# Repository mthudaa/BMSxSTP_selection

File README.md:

# BMSxSTP_selection
This repository used for BMS project at STP ITS selection purpose

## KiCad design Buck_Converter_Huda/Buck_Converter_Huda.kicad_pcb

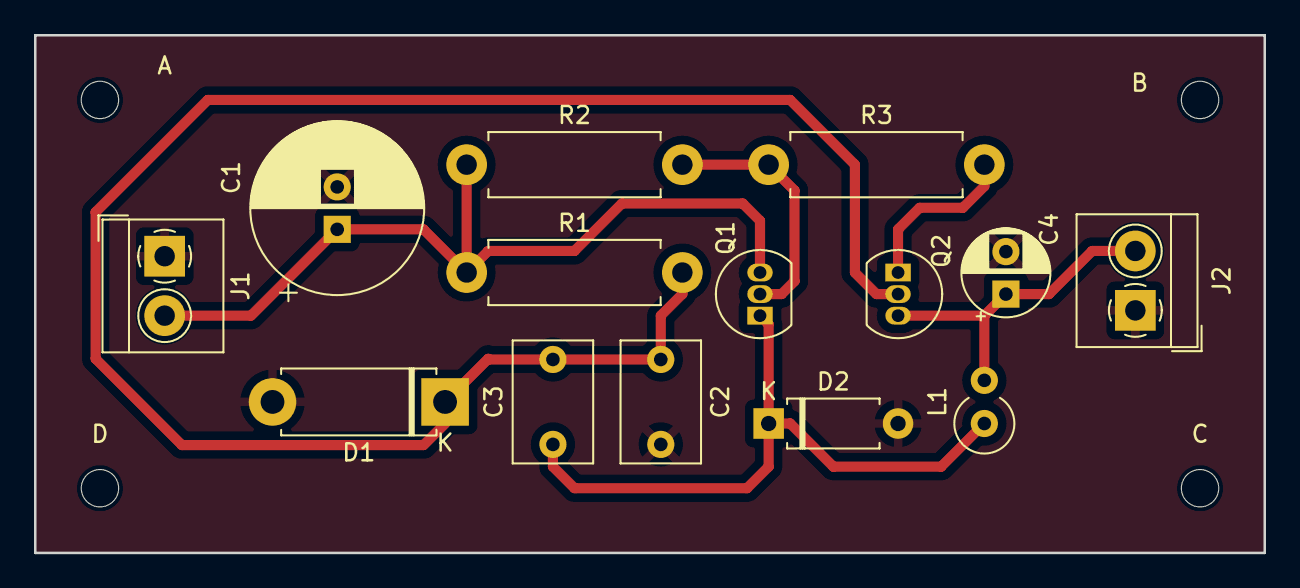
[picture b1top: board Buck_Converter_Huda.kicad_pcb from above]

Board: 2 copper layers, 72.4 x 30.5 mm, 18 parts (0 on the bottom side), 7 nets.

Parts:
A: MountingHole_2.2mm_M2
B: MountingHole_2.2mm_M2
C: MountingHole_2.2mm_M2
C1: 100u; CP_Radial_D10.0mm_P2.50mm
C2: 6.8n; C_Rect_L7.0mm_W4.5mm_P5.00mm
C3: 2n; C_Rect_L7.0mm_W4.5mm_P5.00mm
C4: 47u; CP_Radial_D5.0mm_P2.50mm
D: MountingHole_2.2mm_M2
D1: D_Zener; D_5W_P10.16mm_Horizontal
D2: D_Schottky; D_A-405_P7.62mm_Horizontal
J1: Input; TerminalBlock_4Ucon_1x02_P3.50mm_Horizontal
J2: output; TerminalBlock_4Ucon_1x02_P3.50mm_Horizontal
L1: 2.2m; L_Axial_L7.0mm_D3.3mm_P2.54mm_Vertical_Fastron_MICC
Q1: BC327; TO-92_Inline
Q2: BC337; TO-92_Inline
R1: 4.7k; R_Axial_DIN0411_L9.9mm_D3.6mm_P12.70mm_Horizontal
R2: 470; R_Axial_DIN0411_L9.9mm_D3.6mm_P12.70mm_Horizontal
R3: 2.7k; R_Axial_DIN0411_L9.9mm_D3.6mm_P12.70mm_Horizontal

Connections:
/VIN: C1.1, J1.2, Q1.3 (E), R1.1, R2.1
/VOUT: C4.1, J2.2, L1.2, Q2.3 (E)
GND: C1.2, C2.2, C4.2, D1.2 (A), D2.2 (A), J1.1, J2.1
unnamed: C2.1, C3.2, D1.1 (K), Q2.2 (B), R1.2
unnamed: C3.1, D2.1 (K), L1.1, Q1.1 (C)
unnamed: Q1.2 (B), R2.2, R3.1
unnamed: Q2.1 (C), R3.2

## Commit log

2023-08-13 Update Projek KiCad
2023-08-13 Update Projek STM32
2023-08-13 update terakhir
